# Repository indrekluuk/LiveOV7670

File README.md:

# LiveOV7670
  
Demo:  
https://www.youtube.com/watch?v=TqSY6FETuos&list=PLVilroPGLJaesaS5mP93i0goPck2JK-O4&index=2  
  
Step-by-step guide with pictures:  
https://circuitjournal.com/arduino-ov7670-10fps  
  
Tutorial 1 (10fps video stream to a display):  
https://www.youtube.com/watch?v=Dp3RMb0e1eA&index=3&list=PLVilroPGLJaesaS5mP93i0goPck2JK-O4  
Tutorial 2 (sending image to the PC over the USB cable):  
https://www.youtube.com/watch?v=L9DTW1ulsT0&index=5&list=PLVilroPGLJaesaS5mP93i0goPck2JK-O4  
  
Datasheet for OV7670:  
https://www.voti.nl/docs/OV7670.pdf  

-------------------------------------------------------------------------------  
  
Compiling in Arduino IDE:  
  
1. Download all files
2. copy "src/lib/LiveOV7670Library" and "src/lib/Adafruit_GFX_Library" to Arduino "libraries" folder (If you already have "Adafruit_GFX_Library" then you don't have to copy that)
3. Open "src/LiveOV7670/LiveOV7670.ino" in Arduino IDE
4. Select Tools->Board->Arduino Uno/Nano
  
-------------------------------------------------------------------------------

Connection shcema for the PCB board:  
https://raw.githubusercontent.com/indrekluuk/LiveOV7670/master/LiveOV7670.png

-------------------------------------------------------------------------------
  
### Connections for Arduino Uno/Nano  
  
OV7670 connections:  
  
VSYNC - PIN2  
XCLCK - PIN3 (must be level shifted from 5V -> 3.3V)  
PCLCK - PIN12  
SIOD  - A4 (I2C data) - 10K resistor to 3.3V  
SIOC  - A5 (I2C clock) - 10K resistor to 3.3V  
D0..D3 - A0..A3 (pixel data bits 0..3)  
D4..D7 - PIN4..PIN7 (pixel data bits 4..7)  
3.3V  - 3.3V  
RESET - 3.3V  
GND   - GND  
PWDN  - GND  
  
1.8" TFT connections:  
  
DC - PIN8 (5V -> 3.3V)  
CS - PIN9 (5V -> 3.3V)  
RESET - PIN10 (5V -> 3.3V)  
SPI data - PIN11 (5V -> 3.3V)  
SPI clock - PIN13 (5V -> 3.3V)  
VCC - 5V/3.3V (depending on jumper position on the TFT board)  
BL - 3.3V  
GND - GND  
  
-------------------------------------------------------------------------------
   
### Connections for Arduino Mega  
  
OV7670 connections:  
  
VSYNC - PIN2  
XCLCK - PIN9 (must be level shifted from 5V -> 3.3V)  
PCLCK - PIN12  
SIOD  - PIN20-SDA (I2C data) - 10K resistor to 3.3V  
SIOC  - PIN21-SCL (I2C clock) - 10K resistor to 3.3V  
D0..D7 - PIN22..PIN29 (pixel data bits 0..7)  
3.3V  - 3.3V  
RESET - 3.3V  
GND   - GND  
PWDN  - GND  
  
1.8" TFT connections:  
  
DC - PIN48 (5V -> 3.3V)  
CS - PIN53 (5V -> 3.3V)  
RESET - PIN49 (5V -> 3.3V)  
SPI data - PIN51 (5V -> 3.3V)  
SPI clock - PIN52 (5V -> 3.3V)  
VCC - 5V/3.3V (depending on jumper position on the TFT board)  
BL - 3.3V  
GND - GND  
  
-------------------------------------------------------------------------------
  
Special thanks to
https://github.com/ComputerNerd/ov7670-no-ram-arduino-uno

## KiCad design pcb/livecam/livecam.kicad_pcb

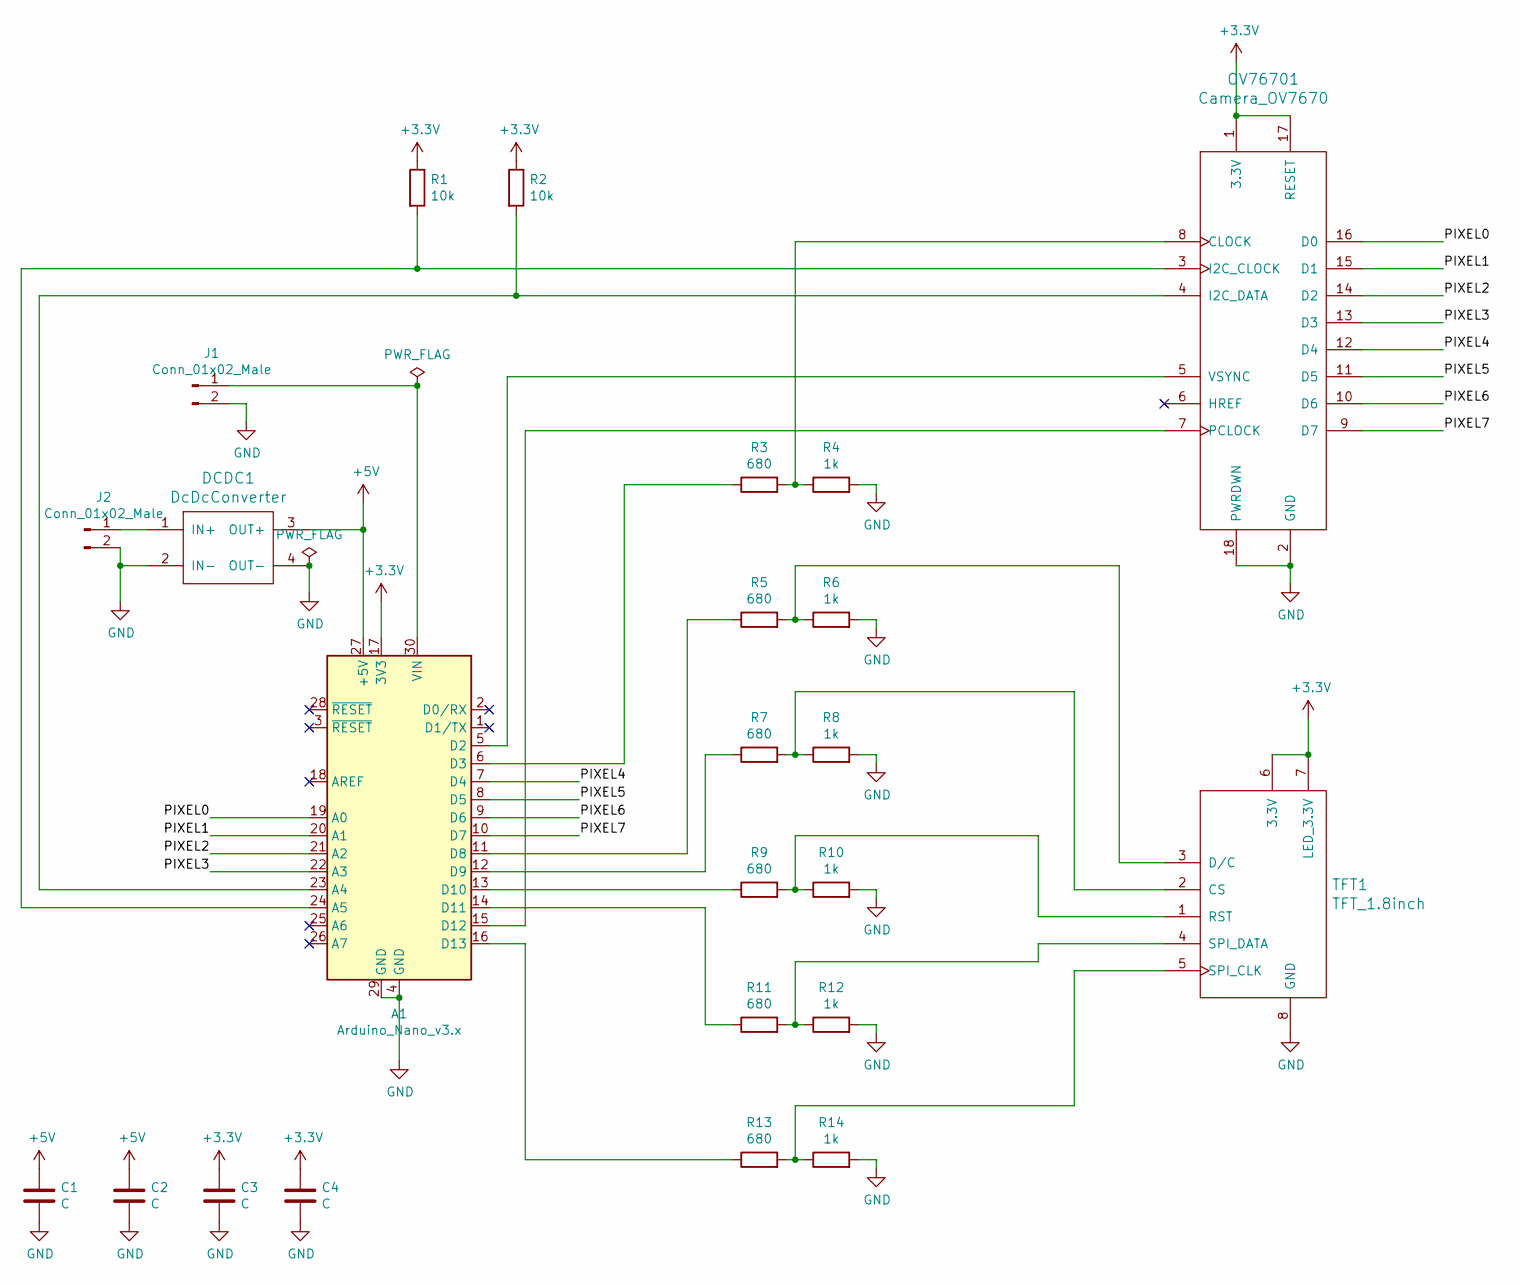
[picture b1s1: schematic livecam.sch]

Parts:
A1: Arduino_Nano_v3.x; Arduino_Nano
C1, C2, C3, C4: C; C_1206_HandSoldering
DCDC1: DcDcConverter; DcDc5VUp
J1, J2: Conn_01x02_Male; Pin_Header_Straight_1x02
OV76701: Camera_OV7670; Pin_Header_Straight_2x09
R1, R2: 10k; R_1206_HandSoldering
R3, R5, R7, R9, R11, R13: 680; R_1206_HandSoldering
R4, R6, R8, R10, R12, R14: 1k; R_1206_HandSoldering
TFT1: TFT_1.8inch; Pin_Header_Straight_1x08

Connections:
+3V3: A1.17 (3V3), C3.1, C4.1, OV76701.1 (3.3V), OV76701.17 (RESET), R1.1, R2.1, TFT1.6 (3.3V), TFT1.7 (LED_3.3V)
+5V: A1.27 (+5V), C1.1, C2.1, DCDC1.3 (OUT+)
/PIXEL0: A1.19 (A0), OV76701.16 (D0)
/PIXEL1: A1.20 (A1), OV76701.15 (D1)
/PIXEL2: A1.21 (A2), OV76701.14 (D2)
/PIXEL3: A1.22 (A3), OV76701.13 (D3)
/PIXEL4: A1.7 (D4), OV76701.12 (D4)
/PIXEL5: A1.8 (D5), OV76701.11 (D5)
/PIXEL6: A1.9 (D6), OV76701.10 (D6)
/PIXEL7: A1.10 (D7), OV76701.9 (D7)
GND: A1.4 (GND), A1.29 (GND), C1.2, C2.2, C3.2, C4.2, DCDC1.2 (IN-), DCDC1.4 (OUT-), J1.2, J2.2, OV76701.2 (GND), OV76701.18 (PWRDWN), R4.2, R6.2, R8.2, R10.2, R12.2, R14.2, TFT1.8 (GND)
unnamed: A1.5 (D2), OV76701.5 (VSYNC)
unnamed: A1.6 (D3), R3.1
unnamed: A1.11 (D8), R5.1
unnamed: A1.12 (D9), R7.1
unnamed: A1.13 (D10), R9.1
unnamed: A1.14 (D11), R11.1
unnamed: A1.15 (D12), OV76701.7 (PCLOCK)
unnamed: A1.16 (D13), R13.1
unnamed: A1.23 (A4), OV76701.4 (I2C_DATA), R2.2
unnamed: A1.24 (A5), OV76701.3 (I2C_CLOCK), R1.2
unnamed: A1.30 (VIN), J1.1
unnamed: DCDC1.1 (IN+), J2.1
unnamed: OV76701.8 (CLOCK), R3.2, R4.1
unnamed: R5.2, R6.1, TFT1.3 (D/C)
unnamed: R7.2, R8.1, TFT1.2 (CS)
unnamed: R9.2, R10.1, TFT1.1 (RST)
unnamed: R11.2, R12.1, TFT1.4 (SPI_DATA)
unnamed: R13.2, R14.1, TFT1.5 (SPI_CLK)

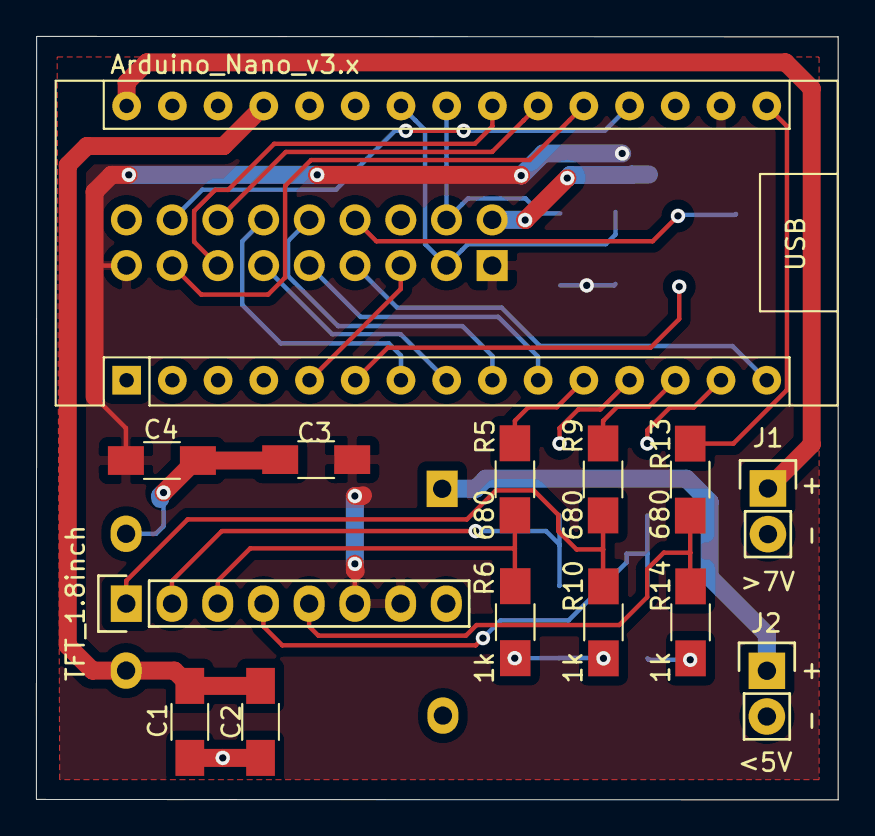
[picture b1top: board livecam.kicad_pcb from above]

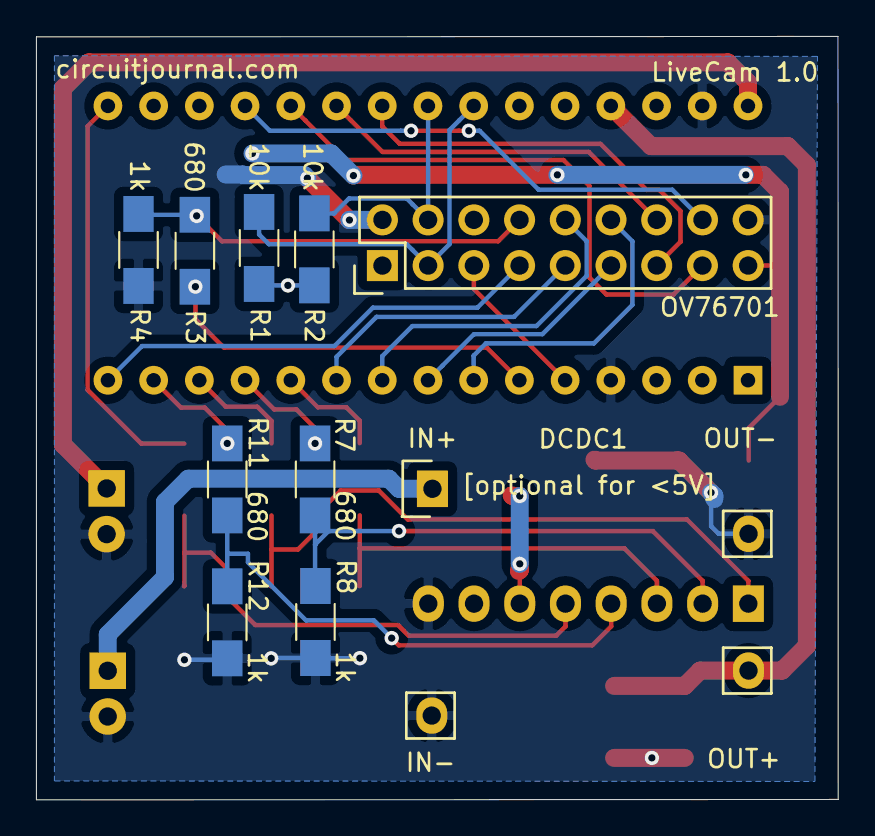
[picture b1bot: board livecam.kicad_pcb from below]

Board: 2 copper layers, 44.5 x 42.4 mm, 24 parts (10 on the bottom side), 29 nets.

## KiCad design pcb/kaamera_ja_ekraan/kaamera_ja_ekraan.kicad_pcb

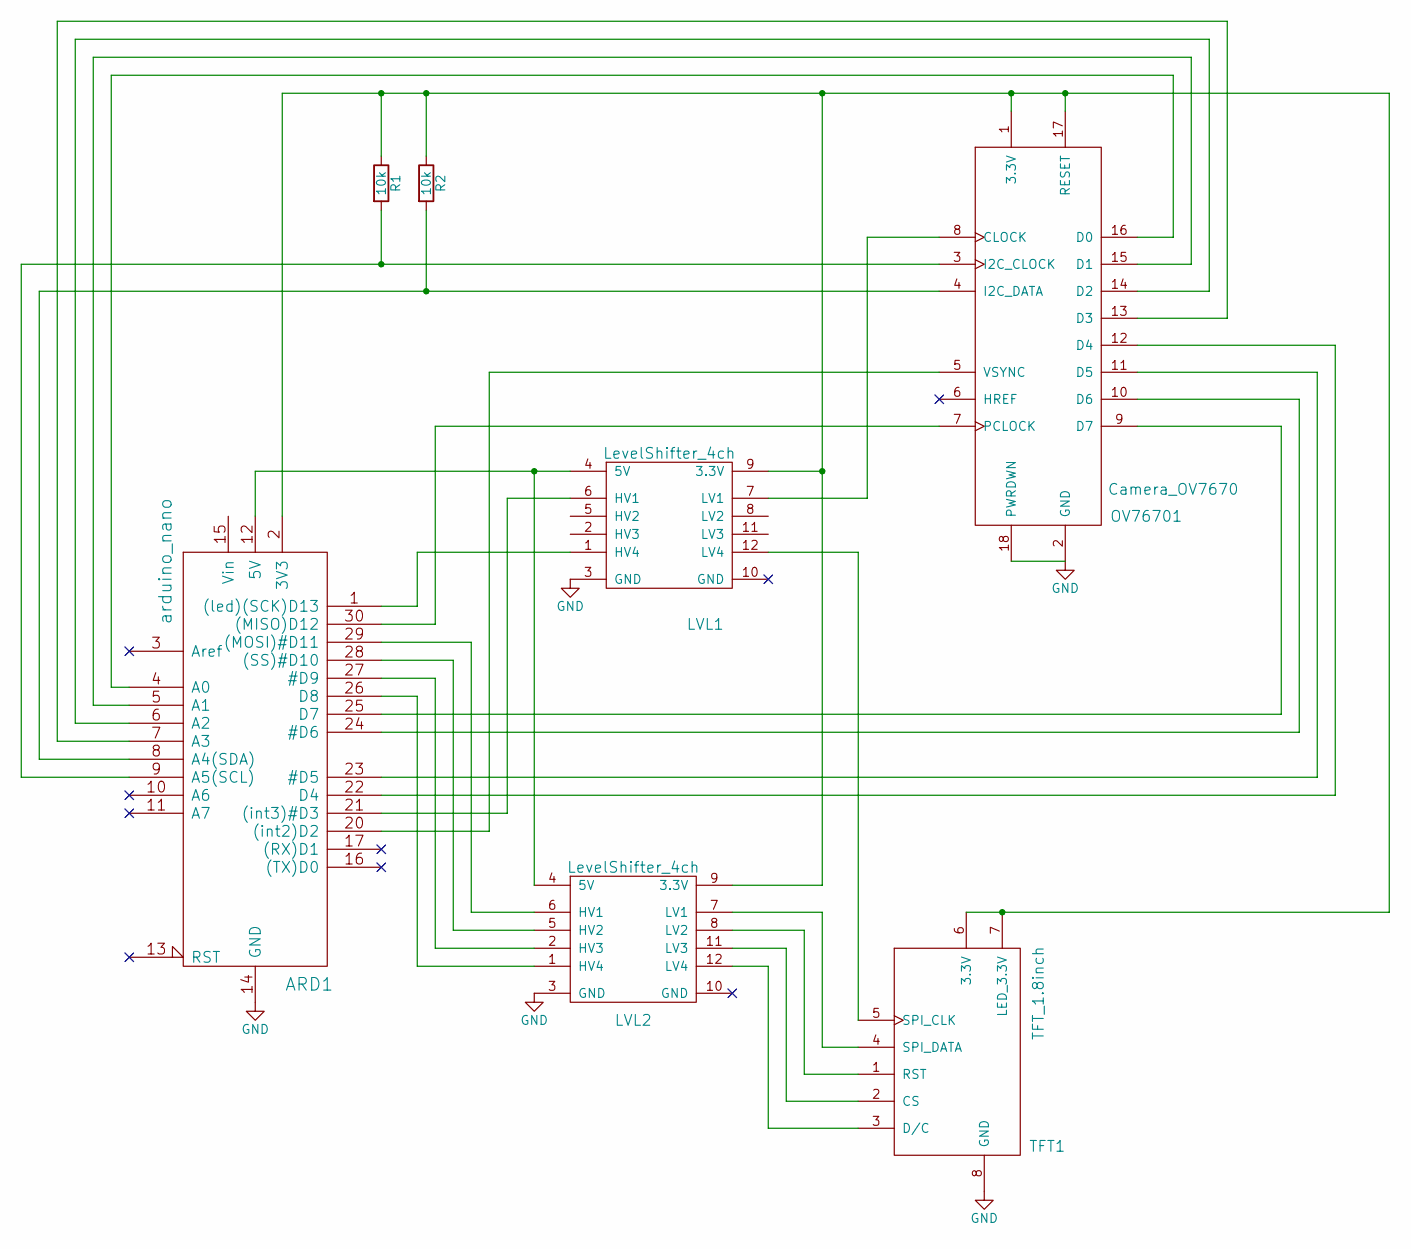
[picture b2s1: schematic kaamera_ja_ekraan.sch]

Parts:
ARD1: arduino_nano; arduino_mini
LVL1, LVL2: LevelShifter_4ch; LevelShifter_2x6_10.16mm
OV76701: Camera_OV7670; Pin_Header_Straight_2x09
R1, R2: 10k; R_1206_HandSoldering
TFT1: TFT_1.8inch; Pin_Header_Straight_1x08

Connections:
GND: ARD1.14 (GND), ARD1.19 (GND), LVL1.3 (GND), LVL2.3 (GND), OV76701.2 (GND), OV76701.18 (PWRDWN), TFT1.8 (GND)
unnamed: ARD1.1 ((led)(SCK)D13), LVL1.1 (HV4)
unnamed: ARD1.2 (3V3), LVL1.9 (3.3V), LVL2.9 (3.3V), OV76701.1 (3.3V), OV76701.17 (RESET), R1.1, R2.1, TFT1.6 (3.3V), TFT1.7 (LED_3.3V)
unnamed: ARD1.4 (A0), OV76701.16 (D0)
unnamed: ARD1.5 (A1), OV76701.15 (D1)
unnamed: ARD1.6 (A2), OV76701.14 (D2)
unnamed: ARD1.7 (A3), OV76701.13 (D3)
unnamed: ARD1.8 (A4(SDA)), OV76701.4 (I2C_DATA), R2.2
unnamed: ARD1.9 (A5(SCL)), OV76701.3 (I2C_CLOCK), R1.2
unnamed: ARD1.12 (5V), LVL1.4 (5V), LVL2.4 (5V)
unnamed: ARD1.20 ((int2)D2), OV76701.5 (VSYNC)
unnamed: ARD1.21 ((int3)#D3), LVL1.6 (HV1)
unnamed: ARD1.22 (D4), OV76701.12 (D4)
unnamed: ARD1.23 (#D5), OV76701.11 (D5)
unnamed: ARD1.24 (#D6), OV76701.10 (D6)
unnamed: ARD1.25 (D7), OV76701.9 (D7)
unnamed: ARD1.26 (D8), LVL2.1 (HV4)
unnamed: ARD1.27 (#D9), LVL2.2 (HV3)
unnamed: ARD1.28 ((SS)#D10), LVL2.5 (HV2)
unnamed: ARD1.29 ((MOSI)#D11), LVL2.6 (HV1)
unnamed: ARD1.30 ((MISO)D12), OV76701.7 (PCLOCK)
unnamed: LVL1.7 (LV1), OV76701.8 (CLOCK)
unnamed: LVL1.12 (LV4), TFT1.5 (SPI_CLK)
unnamed: LVL2.7 (LV1), TFT1.4 (SPI_DATA)
unnamed: LVL2.8 (LV2), TFT1.1 (RST)
unnamed: LVL2.11 (LV3), TFT1.2 (CS)
unnamed: LVL2.12 (LV4), TFT1.3 (D/C)

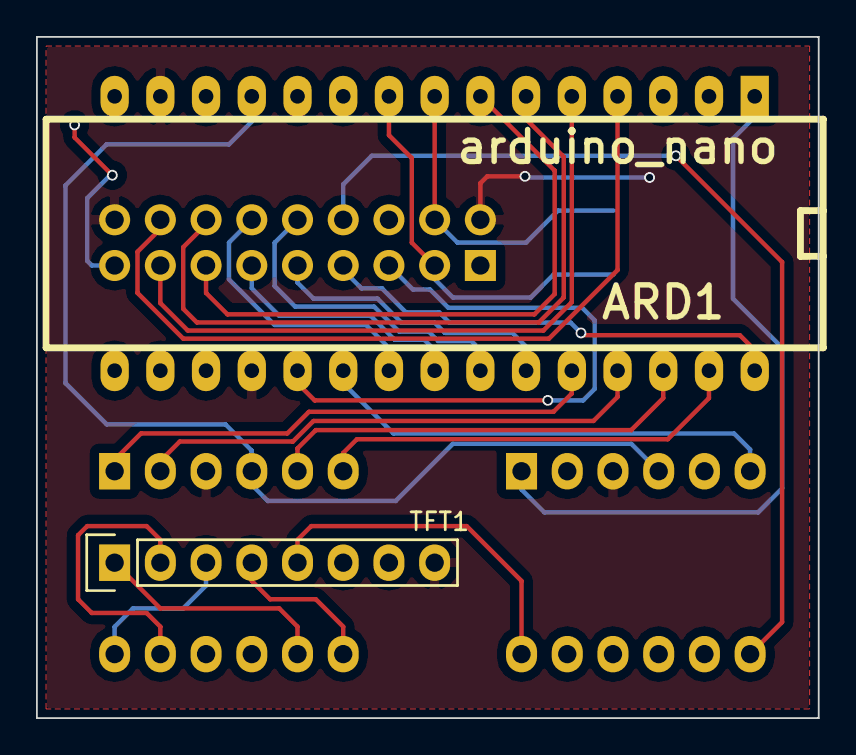
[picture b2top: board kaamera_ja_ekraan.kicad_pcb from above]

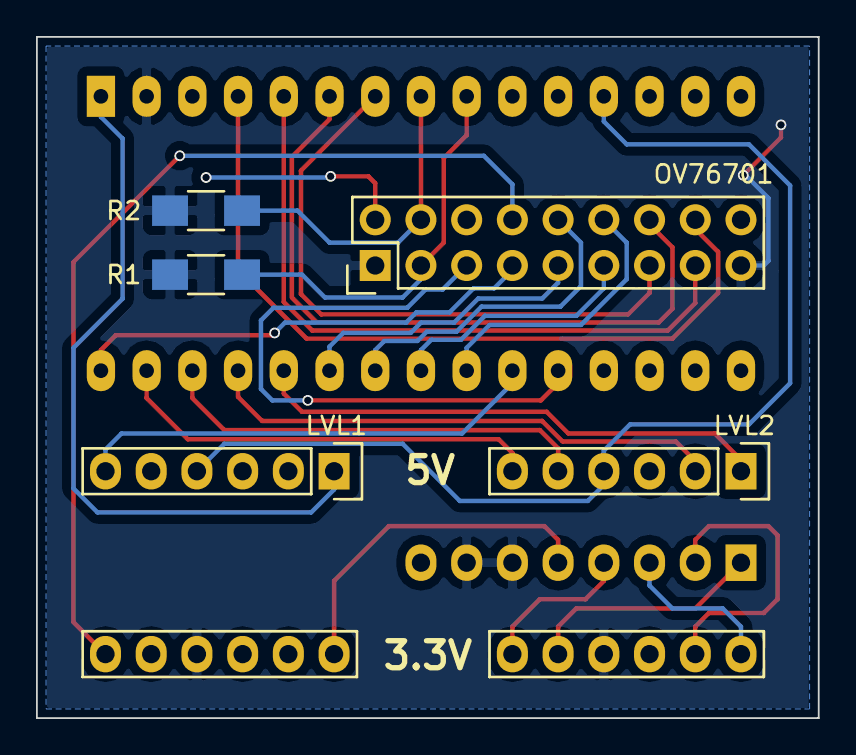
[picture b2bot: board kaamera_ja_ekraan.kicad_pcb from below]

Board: 2 copper layers, 43.4 x 37.8 mm, 7 parts (5 on the bottom side), 27 nets.

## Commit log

2016-04-17 removed unnecessary include
2016-04-17 comment
2016-04-17 fixed pixels on the edge of the screen
2016-04-17 previous version actually has better readability
2016-04-17 better readability
2016-04-18 faster clock speed
2016-04-19 further optimizations
2016-04-19 better logic for writing to TFT
2016-04-19 more optimizations
2016-04-19 different configurations for different speeds
2016-04-19 spacing
2016-04-21 added KiCad project
2016-04-30 refactored and cleaned-up code
2016-04-30 fixed paths in CMakeList
2016-04-30 added missing pin connections
2016-04-30 cleaned up main file
2016-04-30 edited readme.txt
2016-05-01 removed array of clock registers
2016-05-01 added some generic methods and moved QQVGA specific frequencies to its class
2016-05-01 added resolution parameter
2016-05-01 PIN registers can now be pre-defined
2016-05-01 added QVGA up to 2.5Hz
2016-05-01 comments and adjustments
2016-05-01 VGA test
2016-05-01 correct colors for VGA
2016-05-01 Working refresh rates for VGA
2016-05-01 Buffered QQVGA @ 10Hz by default
2016-05-01 CameraOV7670_VGA was probably more confusing than helpful. Removed it.
2016-05-01 moved buffered to sub-folder
2016-05-01 bugfix: last pixel was not sent to screen
2016-05-07 Send data out of UART
2016-06-12 schema
2016-10-29 infrastructure for tests
2016-10-30 More mock friendly camera pin reading
2016-10-30 first functioning tests
2016-10-30 test for writing registers
2016-10-30 fixed compiler warning
2016-10-30 test do not need CMakeLists.txt change to run
2016-10-30 updated read-me to new folder structure
2016-10-30 removed generated files from git
2016-10-30 ignore generated files
2016-10-30 remove generated .gitignore from git
2016-10-30 ignore generated .gitignore
2016-10-30 commented CMakeList.txt in the root directory
2016-10-30 additional camera setup functionality
2016-10-30 test register bits AND/OR
2016-10-30 init all modules at the same time
2016-10-30 test buffered read
2016-10-30 removed unnecessary executable. platformio init will add those automatically
2016-10-30 instruction update
2016-11-06 Buffered grayscale camera with smaller buffer
2016-11-06 For grayscale image buffer shift is not necessary
2016-11-07 buffered grayscale 80x120
2016-11-16 buffer and screen size as constxpr
2016-11-16 Simplified CMakeLists.txt
2016-12-01 80 pixel grayscale does not need unrolled pixel reading
2016-12-01 restored comment
2016-12-01 todo for grayscale
2016-12-01 fixed reading full screen of 80 pixels
2016-12-01 grayscale image does not need to be unrolled
2016-12-13 Moved clock init to Arduino specific macro. Preparation for STM32
2016-12-19 added low light example pictures
2017-01-01 fixed tests
2017-01-01 moved camera code to library
2017-01-01 flattened library
2017-01-01 renamed library folder
2017-02-05 fixed camera object name
2017-02-05 red screen when i2c camera connection fails
2017-02-05 give camera some time to run before starting setup
2017-02-05 show read screen for 3 seconds if i2c fails
2017-02-10 update from STM32 project
2017-02-11 fixed 5Hz
2017-03-02 flash green screen to indicate successful i2c connection to camera
2017-03-19 renamed folders to be more Arduino compatible
2017-03-19 removed option. It is not optional
2017-03-19 Update README.md
    more consistent path name
2017-03-19 more logical and less confusing path names
2017-03-19 remove generated files
2017-03-19 instructions
2017-04-24 upgraded UART sending
2017-05-31 fixed grayscale
2017-06-26 added definition for input initialization
2017-06-29 fixed comment
2017-07-01 Now compiles for Aruduino Mega
2017-11-27 example photos
2017-11-30 set PLL multiplier
2017-12-01 set reverse HREF
2017-12-01 access level
2017-12-01 interlaced Gray scale @20Hz
2017-12-02 only disable timer interrupt
2017-12-02 20Hz grayscale with interrupt
2017-12-02 read PINC out before to get C and D reading closer together
2017-12-02 removed old comment
2018-02-07 Update README.md
    updated url
2018-06-25 method to show color bars
2018-06-25 disable HREF during blank lines
2018-11-16 laser test
2018-11-17 setup for 320x240
2018-11-18 Add files via upload
    additional laser images
2018-11-19 fixed link in comment
2018-11-24 easily selectable UART communication speed and resolution
2018-11-24 new uart image frame format
2018-11-24 fixed slower baud rate
2018-11-24 added configuration for 2M baud rate
2018-11-24 duned UART sending parameters
2018-12-05 do not activate output A (pin 11). It worked with ATMEGA but it broke the code for WAVGAT processor.
2018-12-06 Now works with WAVGAT Nano
2019-01-15 Modes for grayscale image over USB to PC
2019-01-25 Configuration for Arduino Mega
2019-01-25 Configuration for Arduino Mega (added screen support)
2019-01-25 moved delay to mega configuration
2019-01-25 Update README.md
    Connection description for Mega
2019-03-10 Reduce WAVGAT speed to 16Mhz for UART communication
2019-03-14 disable only timer interrupt
2019-07-20 Grayscale VGA for UART
2020-04-26 new PCB
2020-04-26 Generated gerber files
2020-04-26 Re-generated gerber files with version number
2020-04-26 zipped gerber file for upload
2020-08-27 Added Mega support to ExampleGrayscale20HzInterlaced.cpp
2020-08-31 Disable interrupts during frame read only
2020-09-01 Debug command
2020-09-01 Send debug message if frame completes
2020-09-01 Send debug info to computer
2020-09-01 Use length instead of end symbol
2021-08-22 Wait for previous byte to be send instead of waiting for current byte to be sent. This enables more paraller action.
2021-08-22 Removed counter and use uart check instead
2021-08-22 Optimized data sending
2021-08-22 Enable parity check info
2021-08-24 Optimized grayscale processing. 640x480 now works
2021-08-28 Methods for direct register manipulation. Added some constants for registers.
2021-08-28 Better formatting to compare registers
2021-08-28 VGA with padding and padding ignore
2021-08-28 Updated QVGA and QQVGA registers.
2021-08-28 Ignore vertical padding
2021-08-29 Padding to horizontal line
2021-08-29 Fixed line length for grayscale
2021-08-29 VGA wiht 480 + 1 pixels for padding.
2021-08-30 Ignore padding lines for the 10hz example
2021-08-30 Fixed 2hz
2021-08-30 Fixed QVGA 2.5hz
2021-08-30 Fixed qqvga
2021-08-30 Fixed qvga
2021-09-02 Full color VGA
2021-09-02 Fixed Full VGA sending to the screen
2021-09-02 Improved speeds
2021-09-03 More pre-sets for different resolutions and baudrates
2021-09-04 Parity check for grayscale
2021-09-04 Better variable name
2021-09-04 iterate lineBuffer size instead of line length
2021-09-04 Better comments
2021-09-05 Command version 1. removed endOfLine()
2021-09-05 Commands with checksum
2021-09-24 Print "Vsync" when Vsync signal is received
2021-10-17 Updated to new plugin code
